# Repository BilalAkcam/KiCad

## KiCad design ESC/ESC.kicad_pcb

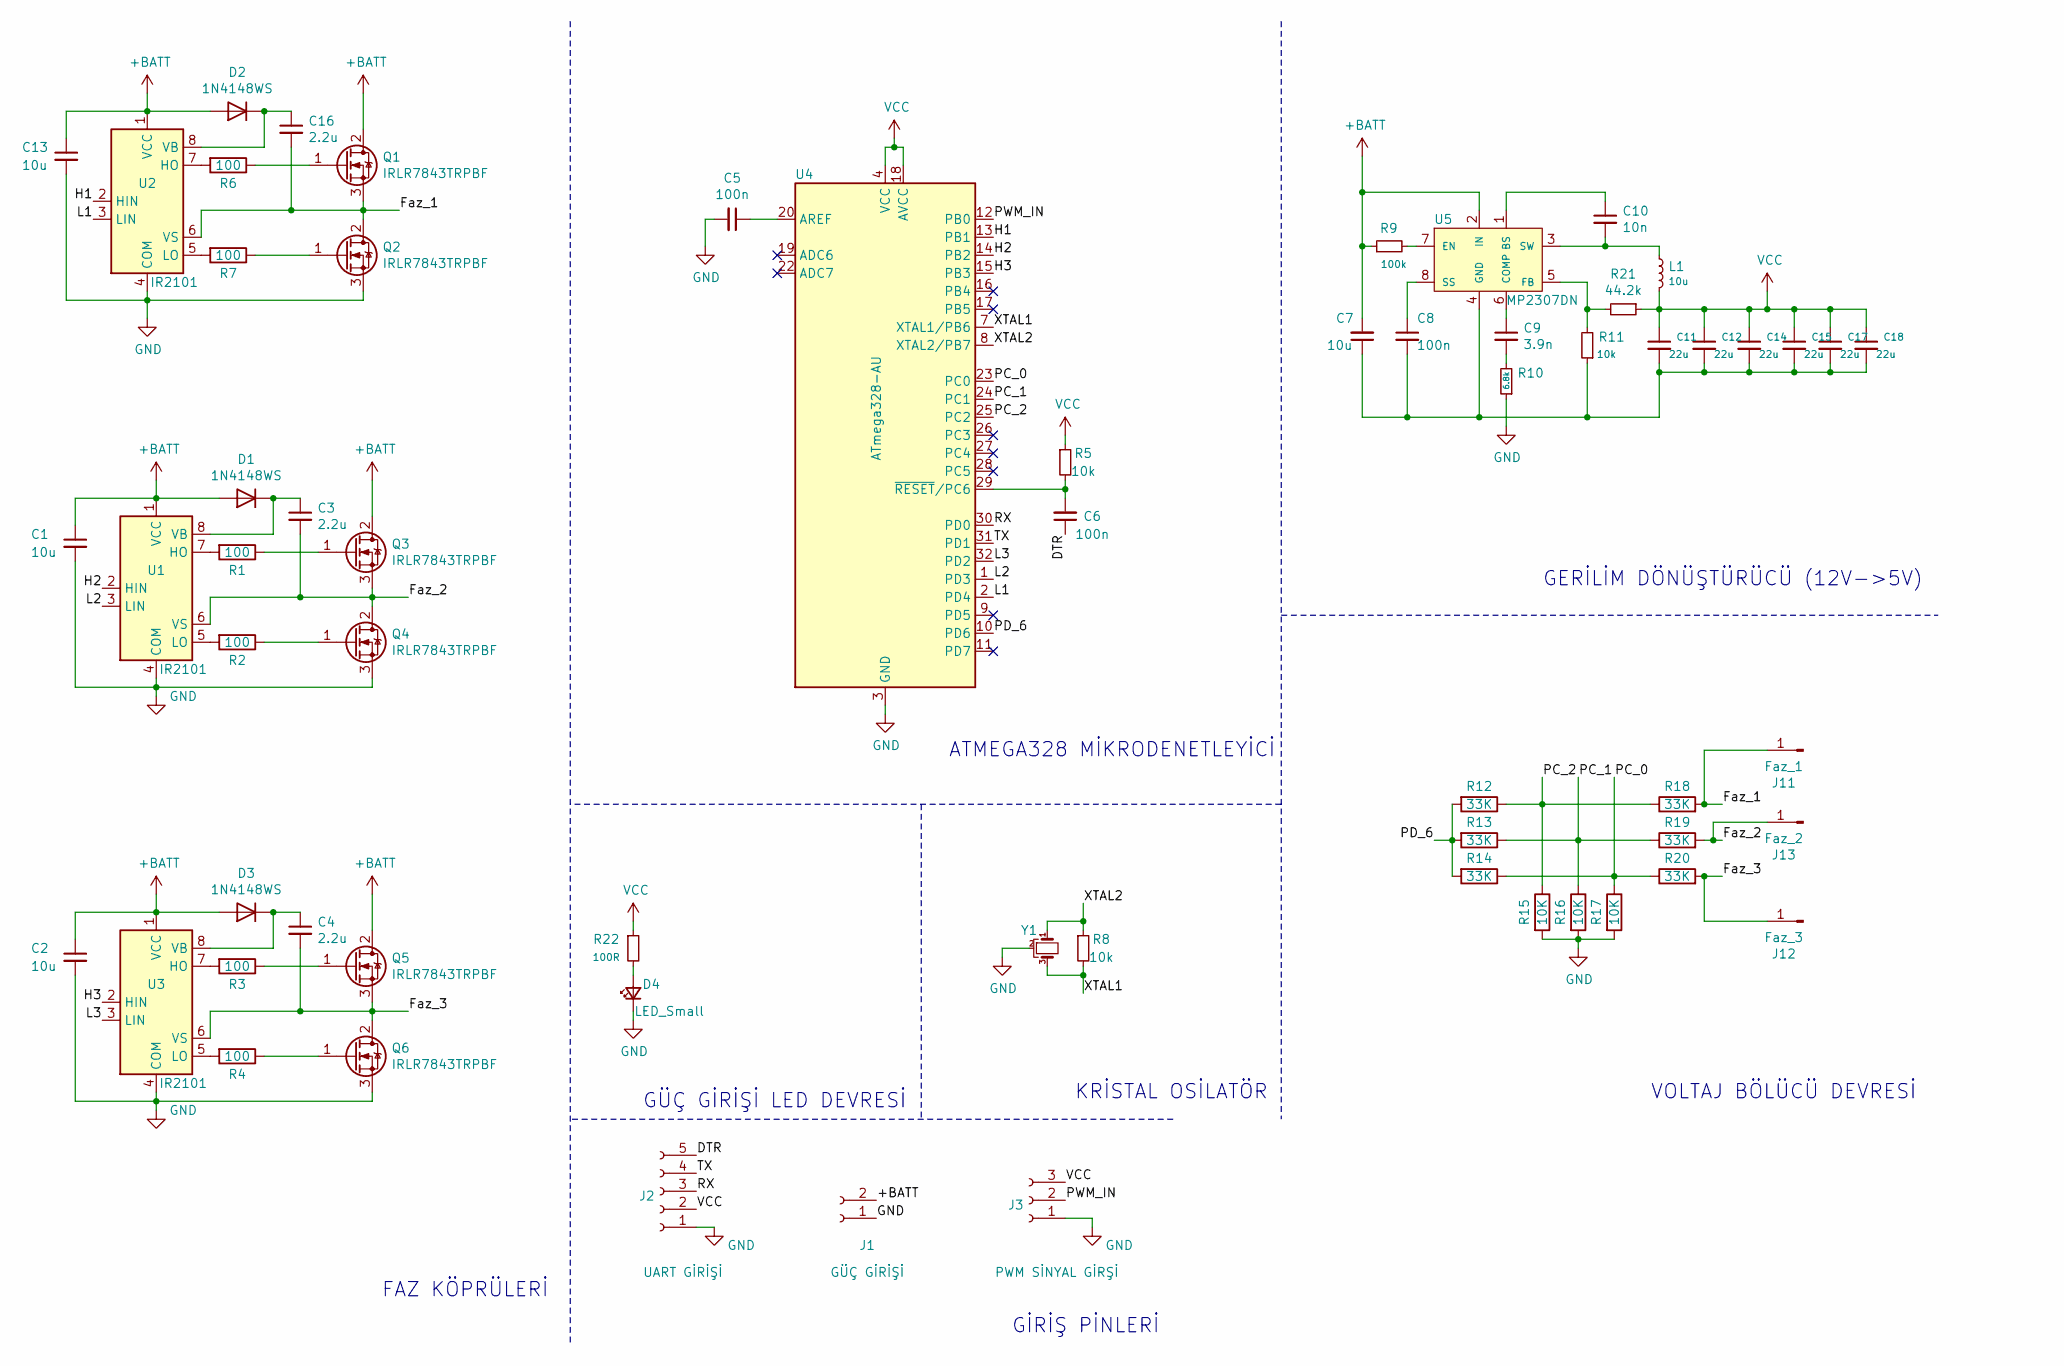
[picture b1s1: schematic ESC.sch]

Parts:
C1, C2, C7, C13: 10u; C_1206_3216Metric_Pad1.33x1.80mm_HandSolder
C3, C4, C16: 2.2u; C_0603_1608Metric_Pad1.08x0.95mm_HandSolder
C5, C6, C8: 100n; C_0603_1608Metric_Pad1.08x0.95mm_HandSolder
C9: 3.9n; C_0603_1608Metric_Pad1.08x0.95mm_HandSolder
C10: 10n; C_0603_1608Metric_Pad1.08x0.95mm_HandSolder
C11, C12, C14, C15, C17, C18: 22u; C_1206_3216Metric_Pad1.33x1.80mm_HandSolder
D1, D2, D3: 1N4148WS; D_SOD-323
D4: LED_Small; LED_0603_1608Metric_Castellated
J1: GÜÇ GİRİŞİ; ESC_IN
J2: UART GİRİŞİ; UART
J3: PWM SİNYAL GİRŞİ; in_pwm
J11: Faz_1; TestPoint_Pad_4.0x4.0mm
J12: Faz_3; TestPoint_Pad_4.0x4.0mm
J13: Faz_2; TestPoint_Pad_4.0x4.0mm
L1: 10u; L_Bourns_SRP7028A_7.3x6.6mm
Q1, Q2, Q3, Q4, Q5, Q6: IRLR7843TRPBF; TO-252-2
R1, R2, R3, R4, R6, R7: 100; R_0603_1608Metric_Pad0.98x0.95mm_HandSolder
R5, R8, R11: 10k; R_0603_1608Metric_Pad0.98x0.95mm_HandSolder
R9: 100k; R_0603_1608Metric_Pad0.98x0.95mm_HandSolder
R10: 6.8k; R_0603_1608Metric_Pad0.98x0.95mm_HandSolder
R12, R13, R14, R18, R19, R20: 33K; R_0603_1608Metric_Pad0.98x0.95mm_HandSolder
R15, R16, R17: 10K; R_0603_1608Metric_Pad0.98x0.95mm_HandSolder
R21: 44.2k; R_0603_1608Metric_Pad0.98x0.95mm_HandSolder
R22: 100R; R_0603_1608Metric_Pad0.98x0.95mm_HandSolder
U1, U2, U3: IR2101; PowerIntegrations_SO-8
U4: ATmega328-AU; TQFP-32_7x7mm_P0.8mm
U5: MP2307DN; Diodes_PSOP-8
Y1: Crystal_GND2_Small; Resonator_SMD_muRata_CSTxExxV-3Pin_3.0x1.1mm

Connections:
+BATT: C1.1, C2.1, C7.2, C13.1, D1.2 (A), D2.2 (A), D3.2 (A), J1.2, Q1.2 (D), Q3.2 (D), Q5.2 (D), R9.1, U1.1 (VCC), U2.1 (VCC), U3.1 (VCC), U5.2 (IN)
/DTR: C6.1, J2.5
/Faz_1: C16.2, J11.1, Q1.3 (S), Q2.2 (D), R18.2, U2.6 (VS)
/Faz_2: C3.2, J13.1, Q3.3 (S), Q4.2 (D), R19.2, U1.6 (VS)
/Faz_3: C4.2, J12.1, Q5.3 (S), Q6.2 (D), R20.2, U3.6 (VS)
/H1: U2.2 (HIN), U4.13 (PB1)
/H2: U1.2 (HIN), U4.14 (PB2)
/H3: U3.2 (HIN), U4.15 (PB3)
/L1: U2.3 (LIN), U4.2 (PD4)
/L2: U1.3 (LIN), U4.1 (PD3)
/L3: U3.3 (LIN), U4.32 (PD2)
/PC_0: R14.1, R17.1, R20.1, U4.23 (PC0)
/PC_1: R13.1, R16.1, R19.1, U4.24 (PC1)
/PC_2: R12.1, R15.1, R18.1, U4.25 (PC2)
/PD_6: R12.2, R13.2, R14.2, U4.10 (PD6)
/PWM_IN: J3.2, U4.12 (PB0)
/RX: J2.3, U4.30 (PD0)
/TX: J2.4, U4.31 (PD1)
/XTAL1: R8.2, U4.7 (XTAL1/PB6), Y1.3
/XTAL2: R8.1, U4.8 (XTAL2/PB7), Y1.1
GND: C1.2, C2.2, C5.2, C13.2, D4.1 (K), J1.3, J2.1, J3.1, Q2.3 (S), Q4.3 (S), Q6.3 (S), R10.1, R15.2, R16.2, R17.2, U1.4 (COM), U2.4 (COM), U3.4 (COM), U4.3 (GND), U4.5 (GND), U4.21 (GND), Y1.2
unnamed: C3.1, D1.1 (K), U1.8 (VB)
unnamed: C4.1, D3.1 (K), U3.8 (VB)
unnamed: C5.1, U4.20 (AREF)
unnamed: C6.2, R5.2, U4.29 (~RESET~/PC6)
unnamed: C8.1, U5.8 (SS)
unnamed: C9.1, U5.6 (COMP)
unnamed: C9.2, R10.2
unnamed: C10.1, U5.1 (BS)
unnamed: C10.2, L1.1, U5.3 (SW)
unnamed: C7.1, C8.2, C11.2, C12.2, C14.2, C15.2, C17.2, C18.2, R11.1, U5.4 (GND)
unnamed: C16.1, D2.1 (K), U2.8 (VB)
unnamed: D4.2 (A), R22.2
unnamed: Q1.1 (G), R6.1
unnamed: Q2.1 (G), R7.1
unnamed: Q3.1 (G), R1.1
unnamed: Q4.1 (G), R2.1
unnamed: Q5.1 (G), R3.1
unnamed: Q6.1 (G), R4.1
unnamed: R1.2, U1.7 (HO)
unnamed: R2.2, U1.5 (LO)
unnamed: R3.2, U3.7 (HO)
unnamed: R4.2, U3.5 (LO)
unnamed: R6.2, U2.7 (HO)
unnamed: R7.2, U2.5 (LO)
unnamed: R9.2, U5.7 (EN)
unnamed: R11.2, R21.2, U5.5 (FB)
VCC: C11.1, C12.1, C14.1, C15.1, C17.1, C18.1, J2.2, J3.3, L1.2, R5.1, R21.1, R22.1, U4.4 (VCC), U4.6 (VCC), U4.18 (AVCC)

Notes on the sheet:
GERİLİM DÖNÜŞTÜRÜCÜ (12V->5V)
GİRİŞ PİNLERİ
VOLTAJ BÖLÜCÜ DEVRESİ
FAZ KÖPRÜLERİ
ATMEGA328 MİKRODENETLEYİCİ
GÜÇ GİRİŞİ LED DEVRESİ
KRİSTAL OSİLATÖR

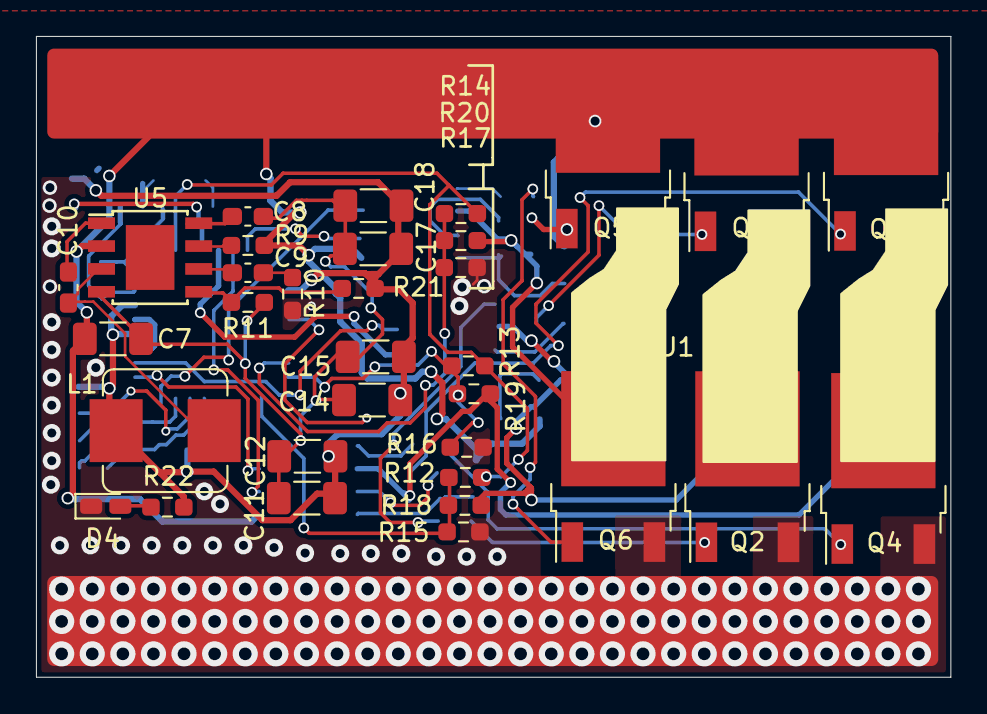
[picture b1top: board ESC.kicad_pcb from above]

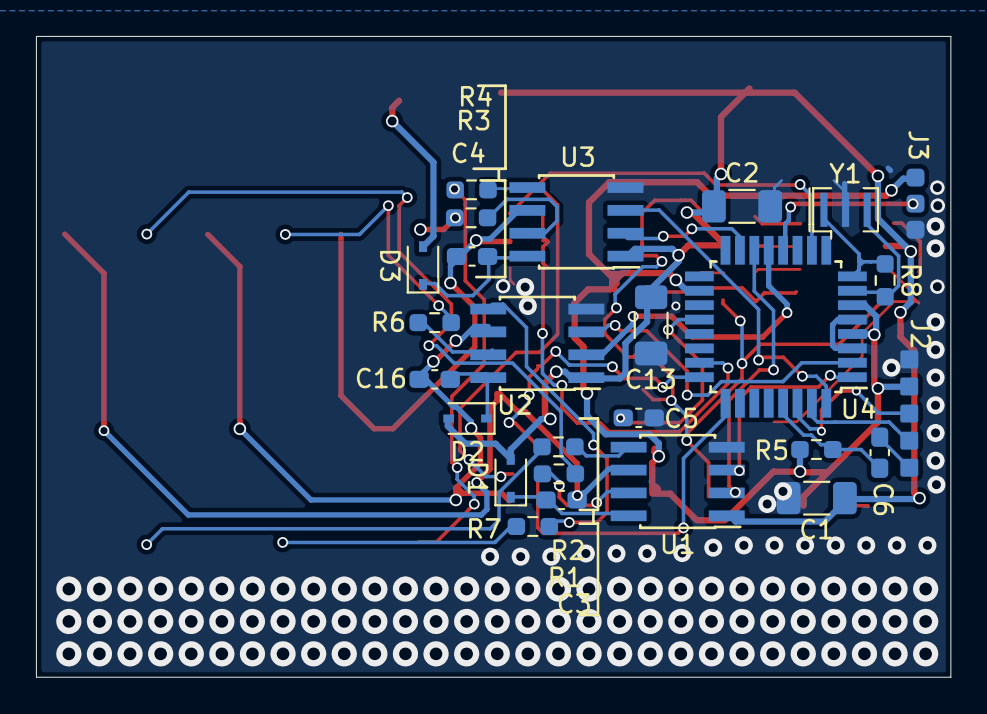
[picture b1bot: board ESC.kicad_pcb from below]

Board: 2 copper layers, 50.8 x 35.6 mm, 63 parts (26 on the bottom side), 48 nets.

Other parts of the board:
J11#2, J11#3: Faz_1; TestPoint_Pad_4.0x4.0mm
